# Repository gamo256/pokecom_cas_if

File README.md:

# pokecom_cas_if

シャープ ポケコン用カセットインターフェース(CE-124相当品)

主な対応機種：
PC-1140, PC-1150
PC-1245, PC-1246, PC-1247, PC-1270
PC-1246S, PC-1246DB, PC-1248, PC-1248DB
PC-1250, PC-1250A, PC-1251, PC-1251H
PC-1252, PC-1252H, PC-1253, PC-1253H
PC-1255, PC-1260, PC-1261, PC-1262
PC-1280, PC-1285
PC-1350, PC-1360, PC-1360K, PC-1365, PC-1365K
PC-1425, PC-1450, PC-1460, PC-1470U, PC-1475
EL-5520
PC-1401, PC-1402, PC-1403, PC-1403H
PC-1404G, PC-1405G, PC-1415G, PC-1416G, PC-1417G
PC-1421, PC-1430, PC-1431, PC-1440, PC-1445
EL-5400, EL-5500, EL-5500II, EL-5500III, EL-5510
PC-1480U, PC-1490U, PC-1490UII, PC-U6000
PC-E500, PC-E500S, PC-E550, PC-E650
PC-1100, PA-500

データレコーダー、または相当品（ICレコーダー、パソコンなど
）への接続には、ステレオミニプラグ（3極,3.5mm）とステレオモノラル変換ケーブルが必要です。

LOAD時は、TIP(Lch)をヘッドフォン出力、CMT出力に接続します。
SAVE時は、RING(Rch)をマイク入力、CMT入力に接続します。

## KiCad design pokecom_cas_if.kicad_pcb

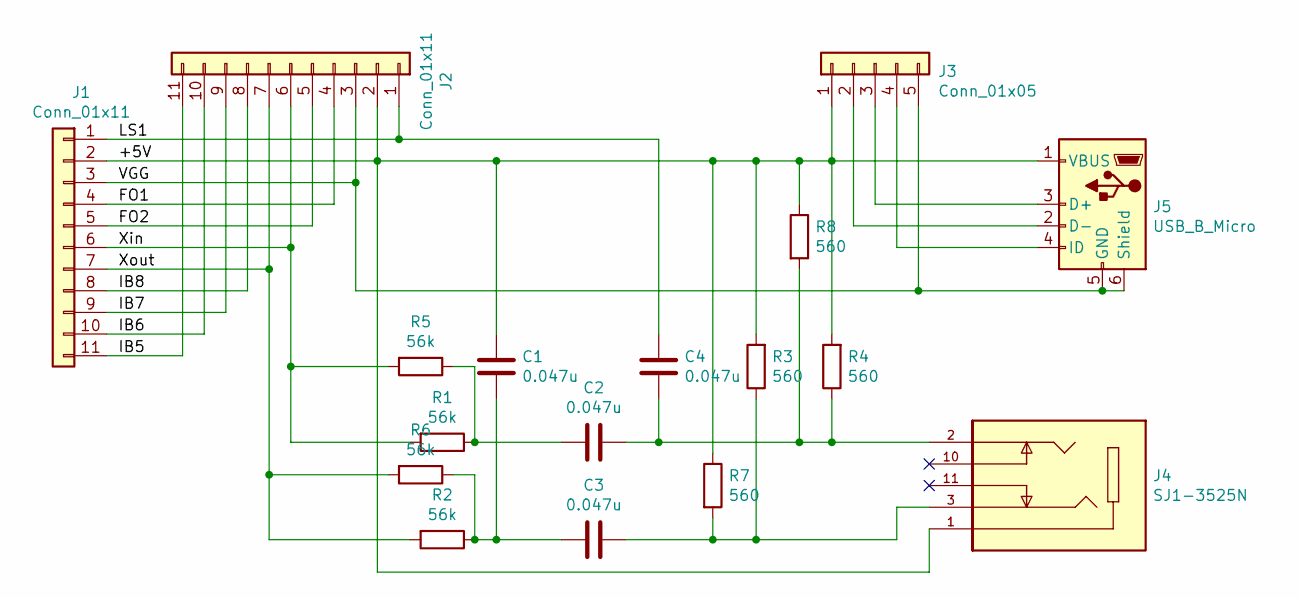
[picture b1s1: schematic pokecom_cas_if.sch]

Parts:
C1, C2, C3, C4: 0.047u; C_Rect_L7.0mm_W3.5mm_P5.00mm
J1: Conn_01x11; PinHeader_1x11_P2.54mm_Horizontal
J2: Conn_01x11; PinHeader_1x11_P2.54mm_Vertical
J3: Conn_01x05; PinHeader_1x05_P2.54mm_Vertical
J4: SJ1-3525N; CUI_SJ1-3525N; PARTREV 1.02
J5: USB_B_Micro; USB_Micro-B_Molex_47346-0001
R1, R2: 56k; R_0603_1608Metric_Pad1.05x0.95mm_HandSolder
R3, R4: 560; R_0603_1608Metric_Pad1.05x0.95mm_HandSolder
R5, R6: 56k; R_Axial_DIN0207_L6.3mm_D2.5mm_P7.62mm_Horizontal
R7, R8: 560; R_Axial_DIN0207_L6.3mm_D2.5mm_P7.62mm_Horizontal

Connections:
/+5V: C1.1, J1.2, J2.2, J3.1, J4.1, J5.1 (VBUS), R3.2, R4.2, R7.1, R8.1
/FO1: J1.4, J2.4
/FO2: J1.5, J2.5
/IB5: J1.11, J2.11
/IB6: J1.10, J2.10
/IB7: J1.9, J2.9
/IB8: J1.8, J2.8
/LS1: C4.2, J1.1, J2.1
/VGG: J1.3, J2.3, J3.5, J5.5 (GND), J5.6 (Shield)
/Xin: J1.6, J2.6, R1.2, R5.2
/Xout: J1.7, J2.7, R2.2, R6.2
unnamed: C1.2, C3.2, R2.1, R6.1
unnamed: C2.1, C4.1, J4.2, R4.1, R8.2
unnamed: C2.2, R1.1, R5.1
unnamed: C3.1, J4.3, R3.1, R7.2
unnamed: J3.2, J5.2 (D-)
unnamed: J3.3, J5.3 (D+)
unnamed: J3.4, J5.4 (ID)

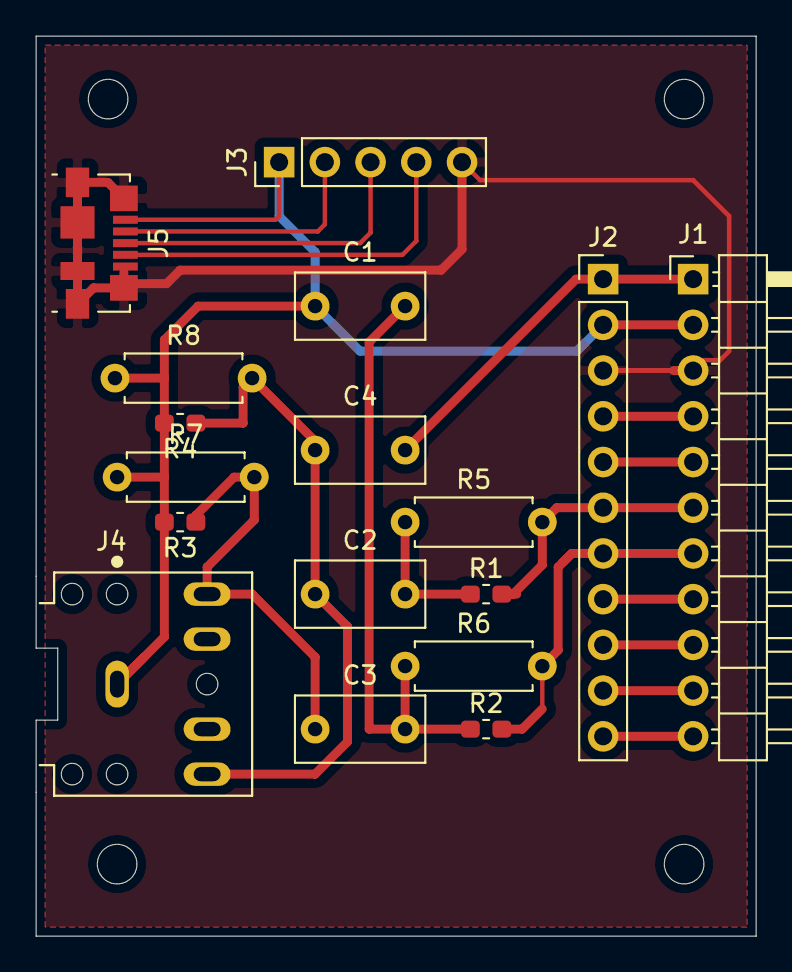
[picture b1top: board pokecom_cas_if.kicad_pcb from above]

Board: 2 copper layers, 40.0 x 50.0 mm, 17 parts (0 on the bottom side), 18 nets.

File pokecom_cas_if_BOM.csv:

Reference, Value, Footprint, Datasheet, MANUFACTURER, PARTREV, STANDARD
J1,Conn_01x11,Connector_PinHeader_2.54mm:PinHeader_1x11_P2.54mm_Horizontal,~,,,
J4,SJ1-3525N,SJ1-3525N:CUI_SJ1-3525N,,CUI,1.02,Manufacturer recommendation
J5,USB_B_Micro,Connector_USB:USB_Micro-B_Molex_47346-0001,~,,,
R1,56k,Resistor_SMD:R_0603_1608Metric_Pad1.05x0.95mm_HandSolder,~,,,
R2,56k,Resistor_SMD:R_0603_1608Metric_Pad1.05x0.95mm_HandSolder,~,,,
R3,560,Resistor_SMD:R_0603_1608Metric_Pad1.05x0.95mm_HandSolder,~,,,
R4,560,Resistor_SMD:R_0603_1608Metric_Pad1.05x0.95mm_HandSolder,~,,,
C2,0.047u,Capacitor_THT:C_Rect_L7.0mm_W3.5mm_P5.00mm,~,,,
C3,0.047u,Capacitor_THT:C_Rect_L7.0mm_W3.5mm_P5.00mm,~,,,
C4,0.047u,Capacitor_THT:C_Rect_L7.0mm_W3.5mm_P5.00mm,~,,,
C1,0.047u,Capacitor_THT:C_Rect_L7.0mm_W3.5mm_P5.00mm,~,,,
J2,Conn_01x11,Connector_PinHeader_2.54mm:PinHeader_1x11_P2.54mm_Vertical,~,,,
J3,Conn_01x05,Connector_PinHeader_2.54mm:PinHeader_1x05_P2.54mm_Vertical,~,,,
R5,56k,Resistor_THT:R_Axial_DIN0207_L6.3mm_D2.5mm_P7.62mm_Horizontal,~,,,
R6,56k,Resistor_THT:R_Axial_DIN0207_L6.3mm_D2.5mm_P7.62mm_Horizontal,~,,,
R7,560,Resistor_THT:R_Axial_DIN0207_L6.3mm_D2.5mm_P7.62mm_Horizontal,~,,,
R8,560,Resistor_THT:R_Axial_DIN0207_L6.3mm_D2.5mm_P7.62mm_Horizontal,~,,,
